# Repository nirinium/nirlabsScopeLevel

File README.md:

# nirlabs Scope Level

An ESP32-based anti-cant level for rifle scopes. Uses an ADXL345 accelerometer to detect tilt and provides real-time LED feedback so you know when your rifle is level before taking a shot.

## Features

- **Three-zone indication** — Level (green), Near-level (green fade + red flash), and Cant (red heartbeat double-pulse)
- **Directional feedback** — Left or right red LED indicates which way you're canted
- **Hysteresis** — Prevents flickering at zone boundaries
- **EMA filtering** — Exponential moving average smooths sensor noise
- **Auto-calibration** — Calibrates on boot assuming the device is held level
- **Battery monitoring** — Low-battery warning via red LED double-blink every 5 seconds
- **Power management** — Enters light sleep after 1 minute at level to conserve battery

## Hardware

| Component | Pin |
|---|---|
| Green LED | GPIO 25 |
| Red LED (Left) | GPIO 26 |
| Red LED (Right) | GPIO 27 |
| Battery voltage divider | GPIO 34 (ADC) |
| ADXL345 SDA | GPIO 21 |
| ADXL345 SCL | GPIO 22 |

**Board:** NodeMCU-32S (ESP32)

## Zone Thresholds

| Zone | Range |
|---|---|
| Level (green solid) | < 0.5° |
| Near level (green fade + red pulse) | 0.5° – 1.5° |
| Cant (red heartbeat) | > 1.5° |

## Build

This project uses [PlatformIO](https://platformio.org/).

```bash
# Build
pio run

# Upload
pio run --target upload

# Serial monitor
pio device monitor
```

### Dependencies

- `Adafruit Unified Sensor` ^1.1.15
- `Adafruit ADXL345` ^1.3.4

## Configuration

Key constants in `src/main.cpp`:

| Constant | Default | Description |
|---|---|---|
| `THRESHOLD` | 0.5° | Dead-level zone boundary |
| `NEAR_ZONE` | 1.5° | Near-level to cant boundary |
| `MAX_CANT` | 5.0° | Maximum urgency angle |
| `HYSTERESIS` | 0.15° | Zone boundary flicker prevention |
| `EMA_ALPHA` | 0.4 | Filter smoothing (lower = smoother) |
| `SLEEP_TIMEOUT` | 60000 ms | Idle time before light sleep |
| `BATT_LOW` | 3.3 V | Low battery warning threshold |
| `DEBUG_MODE` | true | Serial debug output (set false for production) |

## License

NIRINIUM|LABS

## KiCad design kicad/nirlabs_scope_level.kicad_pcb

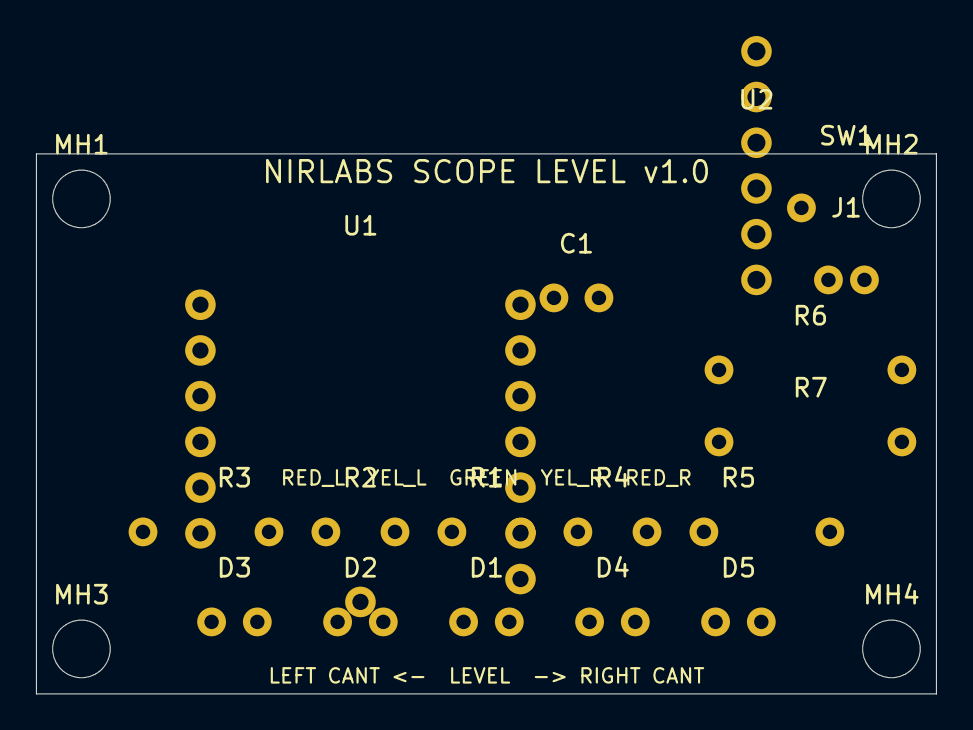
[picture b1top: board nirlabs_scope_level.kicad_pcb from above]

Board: 2 copper layers, 50.0 x 30.0 mm, 21 parts (0 on the bottom side), 17 nets, no tracks yet.

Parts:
C1: 100nF; C_Disc_D3.0mm_W1.6mm_P2.50mm
D1: LED_GREEN; LED_D3.0mm
D2: LED_YEL_L; LED_D3.0mm
D3: LED_RED_L; LED_D3.0mm
D4: LED_YEL_R; LED_D3.0mm
D5: LED_RED_R; LED_D3.0mm
J1: LiPo_JST_PH; JST_PH_S2B-PH-K_1x02_P2.00mm_Horizontal
MH1, MH2, MH3, MH4: MH_3.2mm; MountingHole_3.2mm_M3
R1, R2, R3, R4, R5: 100R; R_Axial_DIN0207_L6.3mm_D2.5mm_P10.16mm_Horizontal
R6, R7: 100k; R_Axial_DIN0207_L6.3mm_D2.5mm_P10.16mm_Horizontal
SW1: Power_Slide_SW; SW_Slide_1P2T_CK_OS102011MA1QN1
U1: XIAO_ESP32C3
U2: ADXL345_Breakout; PinHeader_1x06_P2.54mm_Vertical

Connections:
+3V3: C1.1, U1.7, U2.1, U2.3
GND: C1.2, D1.1, D2.1, D3.1, D4.1, D5.1, J1.2, R7.2, U1.8, U1.14, U2.2
GPIO2_BATT: R6.2, R7.1, U1.1
GPIO3_RL: R3.1, U1.2
GPIO4_YR: R4.1, U1.3
GPIO5_RR: R5.1, U1.4
GPIO6_SDA: U1.5, U2.5
GPIO7_SCL: U1.6, U2.6
GPIO10_SW: SW1.2, U1.13
GPIO20_YL: R2.1, U1.10
GPIO21_GR: R1.1, U1.9
LED_GREEN_A: D1.2, R1.2
LED_RL_A: D3.2, R3.2
LED_RR_A: D5.2, R5.2
LED_YL_A: D2.2, R2.2
LED_YR_A: D4.2, R4.2
VBATT: J1.1, R6.1, SW1.1

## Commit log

2026-04-20 init
2026-04-25 chgs
2026-05-02 lots chjanges
